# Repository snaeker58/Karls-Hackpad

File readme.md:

# Karl's Hackpad - The Cost Effective

## Features
- 20 mechanical keys
- per key a adressable RGB (SK6805)
- XIAO Seed RP2040 MCU
- lots of love
- via support

## Description
This board was designed to deliver maximum keyboard input with no gimmicks or other inputs.
The addressable RGB allows for software based versatility using VIA. Any custom keycaps (or regular keycaps with some tape) and custom set lighting for each key make sure I can use this for anything that needs its own key!
This was made for the Hackclub Hackpad Event, more infos here: [The Hackpad Offical Website](https://hackpad.hackclub.com/).
This keyboard is enabled through qmk and VIA please give them a star [here](https://github.com/qmk/qmk_firmware) and [here](https://github.com/the-via/releases)!

## Images
Front Render:

Back Render:

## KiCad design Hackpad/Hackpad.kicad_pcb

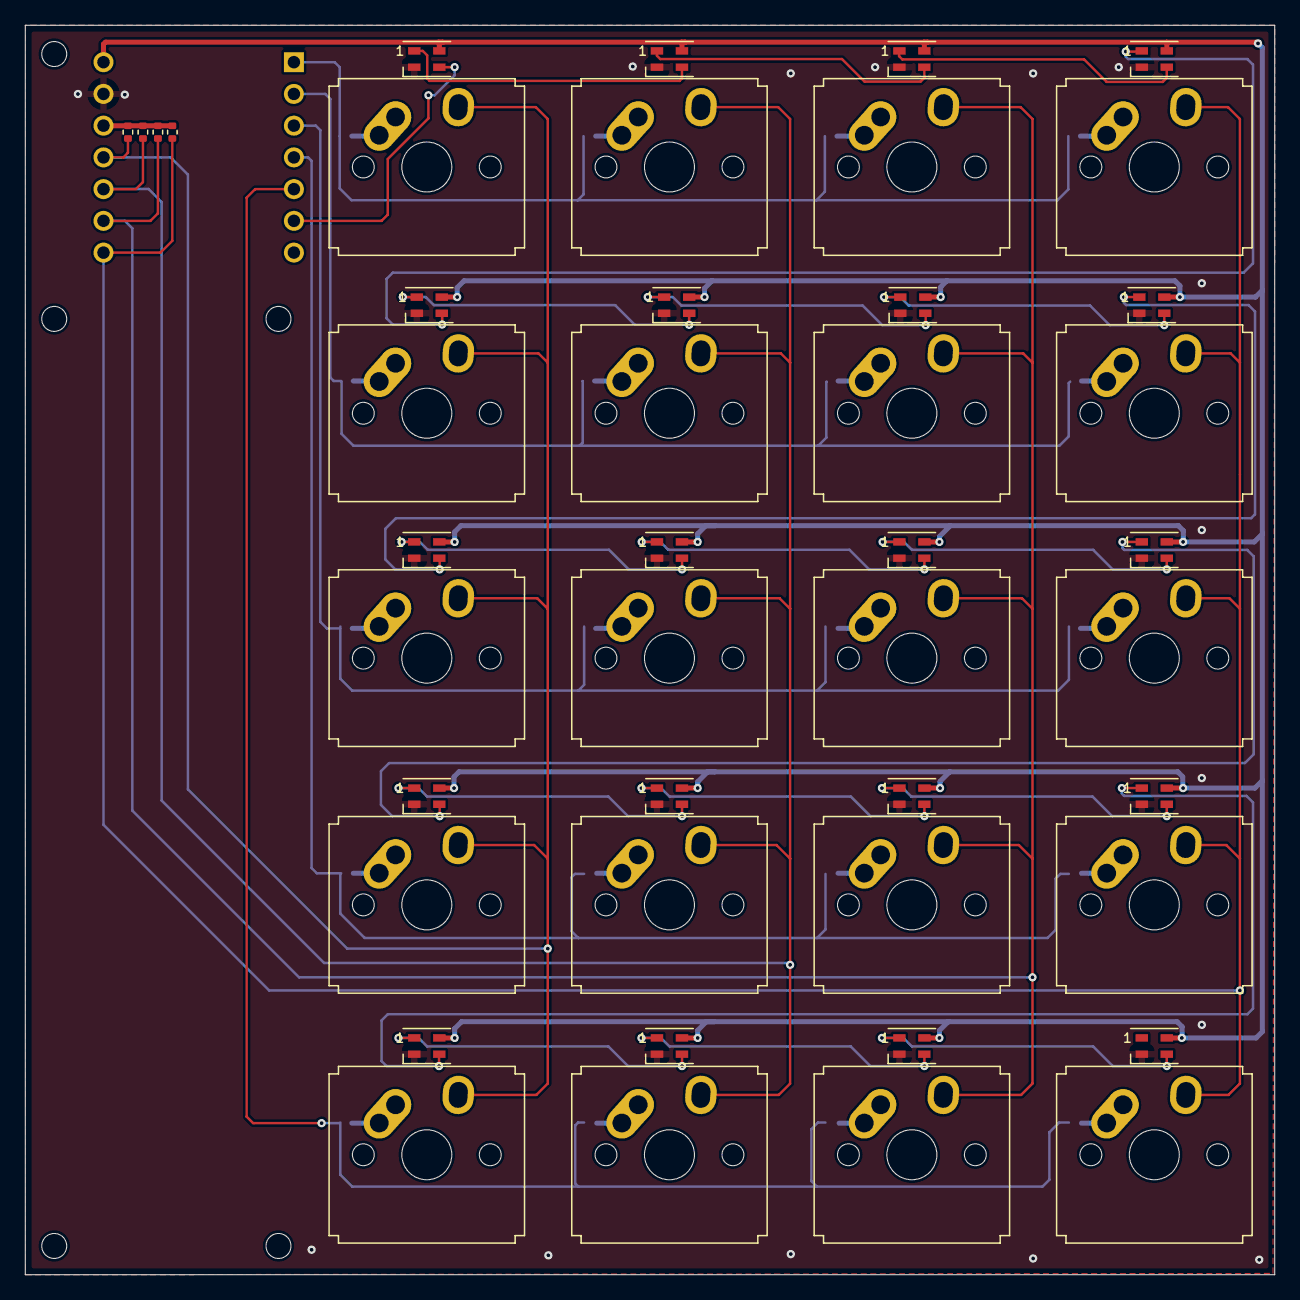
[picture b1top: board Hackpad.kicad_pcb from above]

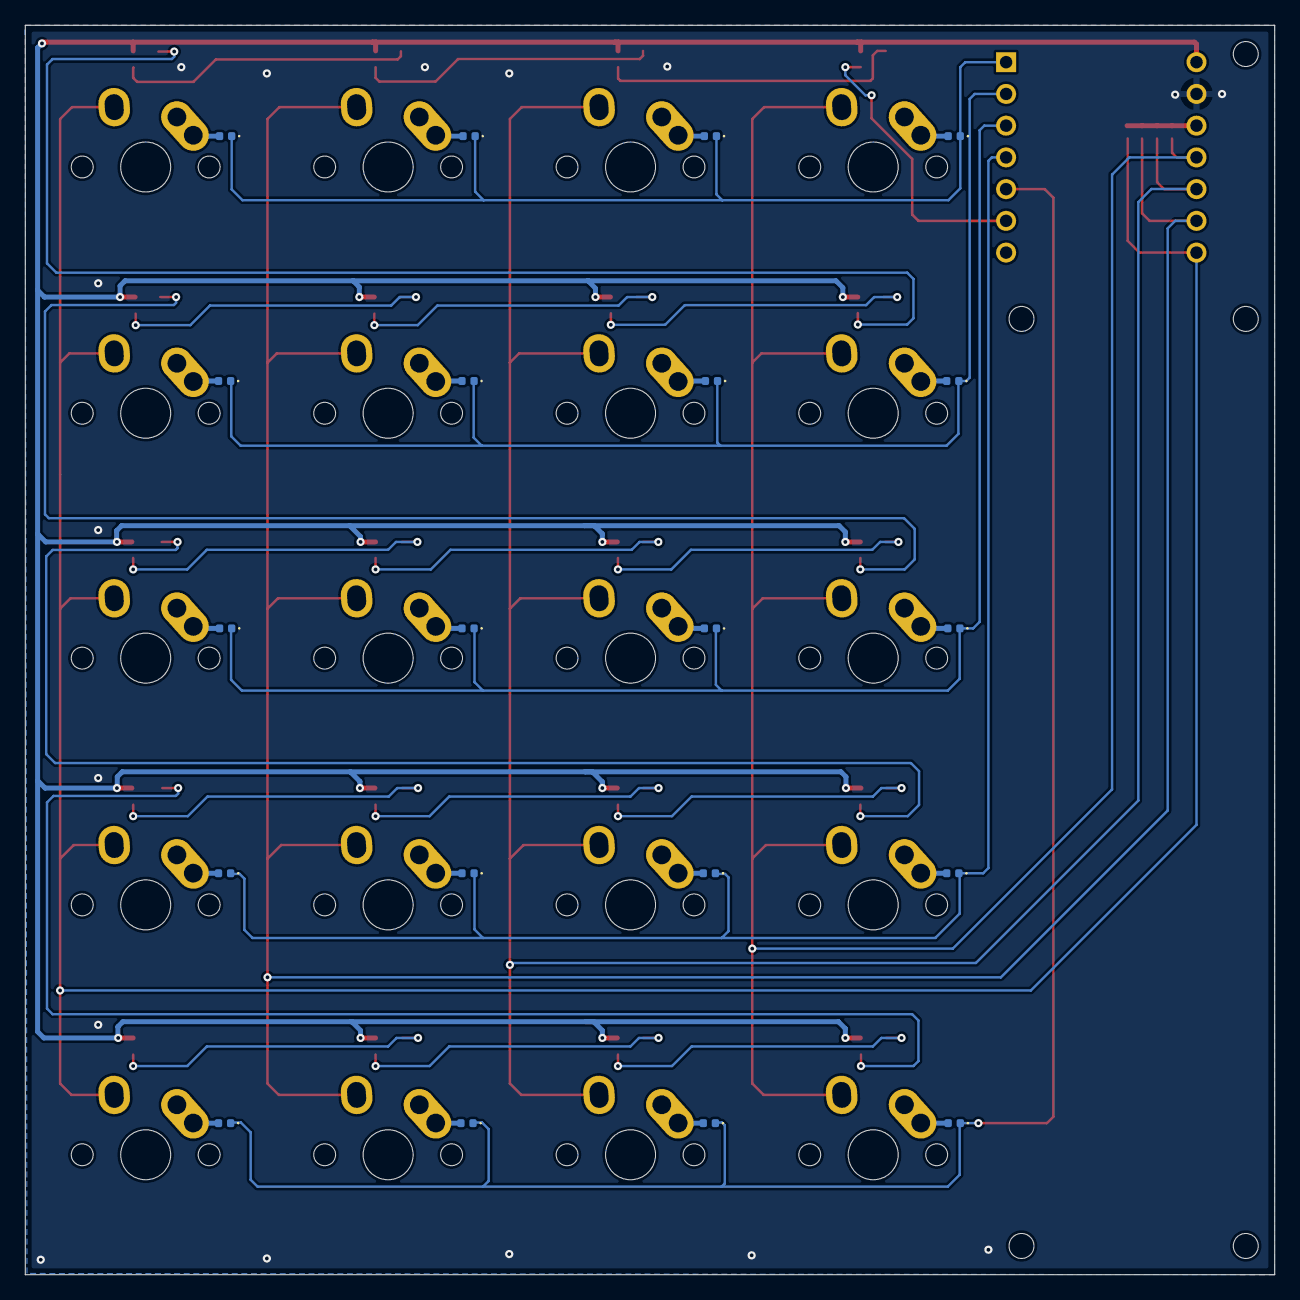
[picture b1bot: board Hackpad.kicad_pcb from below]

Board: 2 copper layers, 100.0 x 100.0 mm, 70 parts (21 on the bottom side), 52 nets.

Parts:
D1, D2, D3, D4, D5, D11, D12, D13, D14, D15, D21, D22, D23, D24, D25, D31, D32, D33, D34, D35: D; D_0402_1005Metric
D6, D7, D8, D9, D10, D16, D17, D18, D19, D20, D26, D27, D28, D29, D30, D36, D37, D38, D39, D40: SK6805; LED_SK6805_PLCC4_2.4x2.7mm_P1.3mm
H1, H2, H3, H4, H5: Case Mounting Hole; MountingHole_2mm
R1, R2, R3, R4: 10k; R_0402_1005Metric
SW1, SW2, SW3, SW4, SW5, SW6, SW7, SW8, SW9, SW10, SW11, SW12, SW13, SW14, SW15, SW16, SW17, SW18, SW19, SW20: SW_SPST; SW_Hybrid_Cherry_MX_Alps_1.00u
U1: Seeed Studio XIAO 14P; XIAO 14P RP2040

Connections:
+3.3V: R1.1, R2.1, R3.1, R4.1, U1.12 (3V3)
+5V: D6.4 (VDD), D7.4 (VDD), D8.4 (VDD), D9.4 (VDD), D10.4 (VDD), D16.4 (VDD), D17.4 (VDD), D18.4 (VDD), D19.4 (VDD), D20.4 (VDD), D26.4 (VDD), D27.4 (VDD), D28.4 (VDD), D29.4 (VDD), D30.4 (VDD), D36.4 (VDD), D37.4 (VDD), D38.4 (VDD), D39.4 (VDD), D40.4 (VDD), U1.14 (5V)
/D_{0}: D1.1 (K), D11.1 (K), D21.1 (K), D31.1 (K), U1.1 (PA02_A0_D0)
/D_{1}: D2.1 (K), D12.1 (K), D22.1 (K), D32.1 (K), U1.2 (PA4_A1_D1)
/D_{2}: D3.1 (K), D13.1 (K), D23.1 (K), D33.1 (K), U1.3 (PA10_A2_D2)
/D_{3}: D4.1 (K), D14.1 (K), D24.1 (K), D34.1 (K), U1.4 (PA11_A3_D3)
/D_{4}: D5.1 (K), D15.1 (K), D25.1 (K), D35.1 (K), U1.5 (PA8_A4_D4_SDA)
/D_{7}: R4.2, SW16.2, SW17.2, SW18.2, SW19.2, SW20.2, U1.8 (PB09_A7_D7_RX)
/D_{8}: R3.2, SW11.2, SW12.2, SW13.2, SW14.2, SW15.2, U1.9 (PA7_A8_D8_SCK)
/D_{9}: R2.2, SW6.2, SW7.2, SW8.2, SW9.2, SW10.2, U1.10 (PA5_A9_D9_MISO)
/D_{10}: R1.2, SW1.2, SW2.2, SW3.2, SW4.2, SW5.2, U1.11 (PA6_A10_D10_MOSI)
/Keyboard Matrix/Loop_{1}: D7.3 (DIN), D36.1 (DOUT)
/Keyboard Matrix/Loop_{2}: D8.3 (DIN), D37.1 (DOUT)
/Keyboard Matrix/Loop_{3}: D9.3 (DIN), D38.1 (DOUT)
/Keyboard Matrix/Loop_{4}: D10.3 (DIN), D39.1 (DOUT)
/LED: D6.3 (DIN), U1.6 (PA9_A5_D5_SCL)
GND: D6.2 (VSS), D7.2 (VSS), D8.2 (VSS), D9.2 (VSS), D10.2 (VSS), D16.2 (VSS), D17.2 (VSS), D18.2 (VSS), D19.2 (VSS), D20.2 (VSS), D26.2 (VSS), D27.2 (VSS), D28.2 (VSS), D29.2 (VSS), D30.2 (VSS), D36.2 (VSS), D37.2 (VSS), D38.2 (VSS), D39.2 (VSS), D40.2 (VSS), U1.13 (GND)
unnamed: D1.2 (A), SW1.1
unnamed: D2.2 (A), SW2.1
unnamed: D3.2 (A), SW3.1
unnamed: D4.2 (A), SW4.1
unnamed: D5.2 (A), SW5.1
unnamed: D10.1 (DOUT), D20.3 (DIN)
unnamed: D11.2 (A), SW6.1
unnamed: D12.2 (A), SW7.1
unnamed: D13.2 (A), SW8.1
unnamed: D14.2 (A), SW9.1
unnamed: D15.2 (A), SW10.1
unnamed: D6.1 (DOUT), D16.3 (DIN)
unnamed: D16.1 (DOUT), D26.3 (DIN)
unnamed: D7.1 (DOUT), D17.3 (DIN)
unnamed: D17.1 (DOUT), D27.3 (DIN)
unnamed: D8.1 (DOUT), D18.3 (DIN)
unnamed: D18.1 (DOUT), D28.3 (DIN)
unnamed: D9.1 (DOUT), D19.3 (DIN)
unnamed: D19.1 (DOUT), D29.3 (DIN)
unnamed: D20.1 (DOUT), D30.3 (DIN)
unnamed: D21.2 (A), SW11.1
unnamed: D22.2 (A), SW12.1
unnamed: D23.2 (A), SW13.1
unnamed: D24.2 (A), SW14.1
unnamed: D25.2 (A), SW15.1
unnamed: D26.1 (DOUT), D36.3 (DIN)
unnamed: D27.1 (DOUT), D37.3 (DIN)
unnamed: D28.1 (DOUT), D38.3 (DIN)
unnamed: D29.1 (DOUT), D39.3 (DIN)
unnamed: D30.1 (DOUT), D40.3 (DIN)
unnamed: D31.2 (A), SW16.1
unnamed: D32.2 (A), SW17.1
unnamed: D33.2 (A), SW18.1
unnamed: D34.2 (A), SW19.1
unnamed: D35.2 (A), SW20.1

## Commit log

2024-10-06 Added Render
2024-10-07 Added Fusion/CAD files
2024-10-10 Added layout image
2024-10-10 Added firmware
2024-10-11 Added precompiled firmware
2024-10-11 Added BOM
